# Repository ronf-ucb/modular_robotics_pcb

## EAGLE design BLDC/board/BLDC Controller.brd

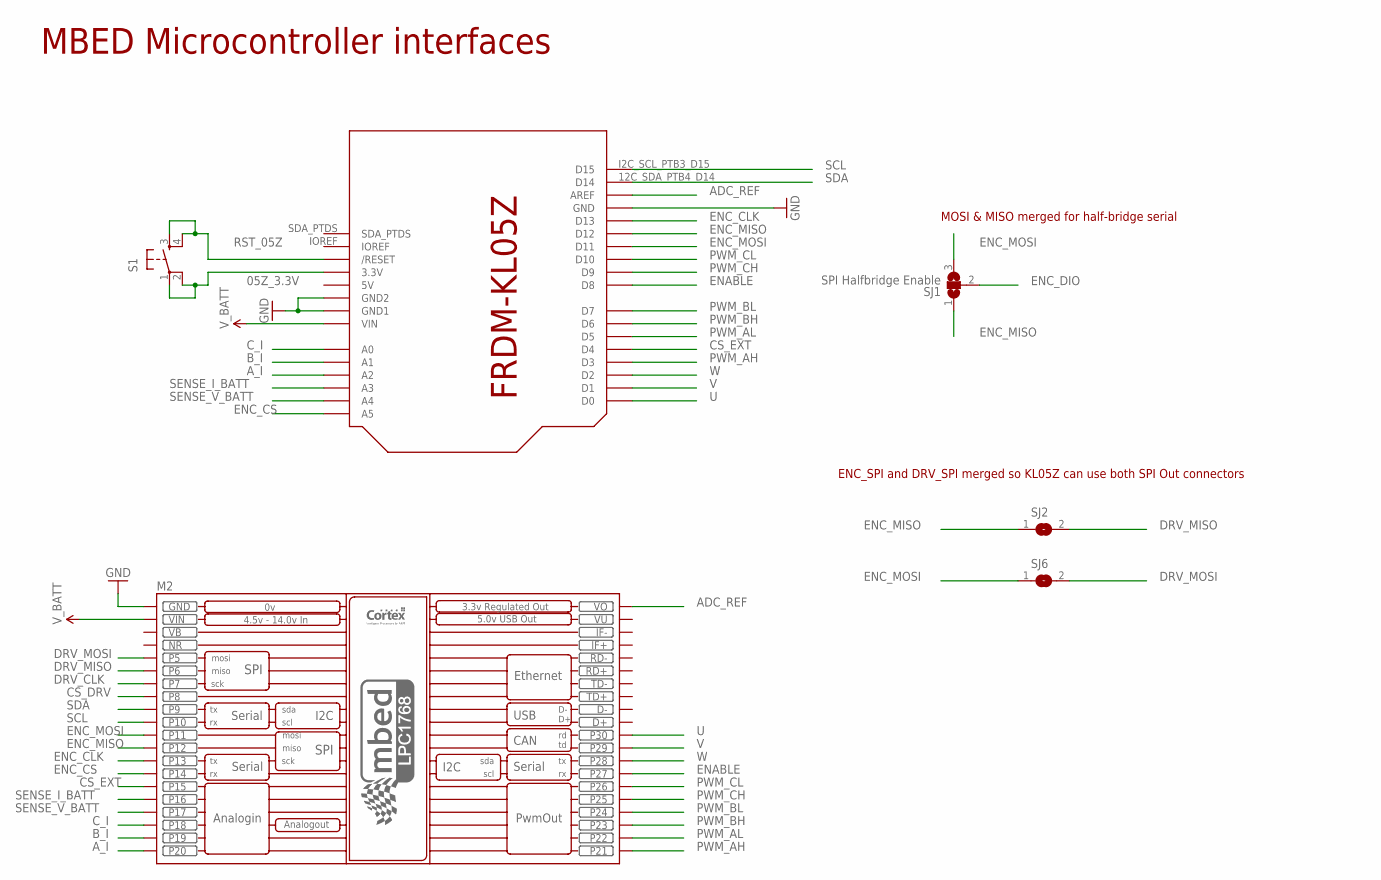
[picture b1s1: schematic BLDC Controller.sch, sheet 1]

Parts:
M1: FRDM-KL05Z; FREESCALEKL05Z
M2: MBED_NXP_LPC1768; MBED-KIT
S1: TAC_SWITCHPTH; TACTILE-PTH
SJ1: SPI Halfbridge Enable; SJ_2
SJ2, SJ6: SJ

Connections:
05Z_3.3V: M1.3.3V, S1.1, S1.2
ADC_REF: M1.AVDD (AREF), M2.VOUT (VO); also elsewhere on the board
A_I: M1.A2_PTA8 (A2), M2.P$20 (P20); also elsewhere on the board
B_I: M1.A1_PTB9 (A1), M2.P$19 (P19); also elsewhere on the board
CS_DRV: M2.P$8 (P8); also elsewhere on the board
CS_EXT: M1.PTA10_D4 (D4), M2.P$15 (P15); also elsewhere on the board
C_I: M1.A0_PTB8 (A0), M2.P$18 (P18); also elsewhere on the board
DRV_CLK: M2.P$7 (P7); also elsewhere on the board
DRV_MISO: M2.P$6 (P6), SJ2.2; also elsewhere on the board
DRV_MOSI: M2.P$5 (P5), SJ6.2; also elsewhere on the board
ENABLE: M1.PTB10_D8 (D8), M2.P$27 (P27); also elsewhere on the board
ENC_CLK: M1.SCK_PTB0_D13 (D13), M2.P$13 (P13); also elsewhere on the board
ENC_CS: M1.A5_PTB13 (A5), M2.P$14 (P14); also elsewhere on the board
ENC_DIO: SJ1.2; also elsewhere on the board
ENC_MISO: M1.MISO_PTA6_D12 (D12), M2.P$12 (P12), SJ1.1, SJ2.1; also elsewhere on the board
ENC_MOSI: M1.MOSI_PTA_D11 (D11), M2.P$11 (P11), SJ1.3, SJ6.1; also elsewhere on the board
GND: M1.GND, M1.GND1, M1.GND2, M2.GND; also elsewhere on the board
NR: M2.NR
PWM_AH: M1.PTB5_D3 (D3), M2.P$21 (P21); also elsewhere on the board
PWM_AL: M1.PTA12_D5 (D5), M2.P$22 (P22); also elsewhere on the board
PWM_BH: M1.PTB6_D6 (D6), M2.P$23 (P23); also elsewhere on the board
PWM_BL: M1.PTB7_D7 (D7), M2.P$24 (P24); also elsewhere on the board
PWM_CH: M1.PTB11_D9 (D9), M2.P$25 (P25); also elsewhere on the board
PWM_CL: M1.PTA_D10 (D10), M2.P$26 (P26); also elsewhere on the board
RST_05Z: M1.RESET (/RESET), S1.3, S1.4
SCL: M1.I2C_SCL_PTB3_D15 (D15), M2.P$10 (P10); also elsewhere on the board
SDA: M1.12C_SDA_PTB4_D14 (D14), M2.P$9 (P9); also elsewhere on the board
SENSE_I_BATT: M1.A3_PTA0 (A3), M2.P$16 (P16); also elsewhere on the board
SENSE_V_BATT: M1.A4_PTA9 (A4), M2.P$17 (P17); also elsewhere on the board
U: M1.TX_PTB2_D0 (D0), M2.P$30 (P30); also elsewhere on the board
V: M1.RX_PTB1_D1 (D1), M2.P$29 (P29); also elsewhere on the board
VB: M2.VB
V_BATT: M1.VIN, M2.VIN; also elsewhere on the board
W: M1.PTA11_D2 (D2), M2.P$28 (P28); also elsewhere on the board

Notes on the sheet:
MBED Microcontroller interfaces
MOSI & MISO merged for half-bridge serial
ENC_SPI and DRV_SPI merged so KL05Z can use both SPI Out connectors

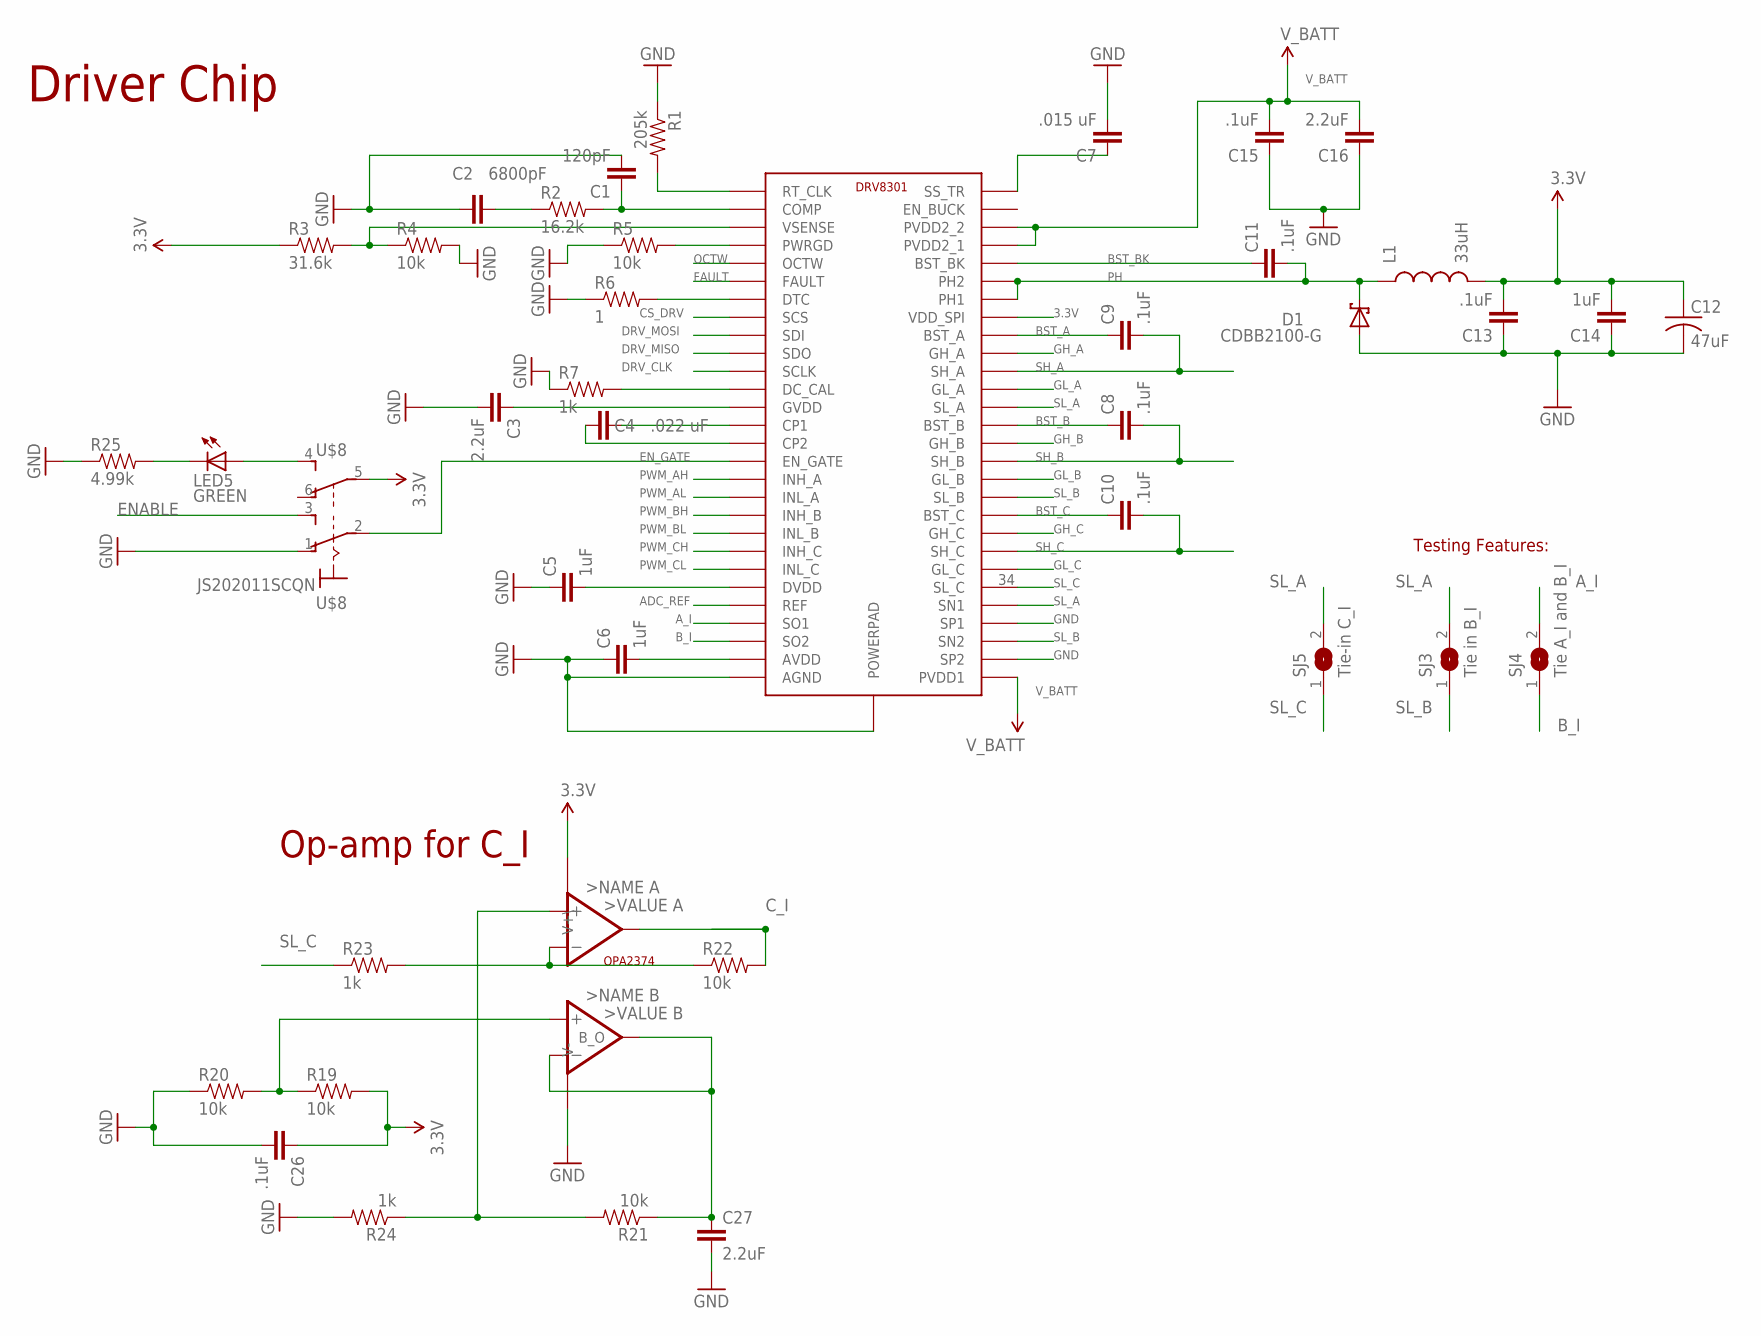
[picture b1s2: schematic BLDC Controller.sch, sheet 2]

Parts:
C1: 120pF; 0402-CAP
C2: 6800pF; 0402-CAP
C3, C16, C27: 2.2uF; 0402-CAP
C4: .022 uF; 0402-CAP
C5, C6, C14: 1uF; 0402-CAP
C7: .015 uF; 0402-CAP
C8, C9, C10, C11, C13, C15, C26: .1uF; 0402-CAP
C12: 47uF; C0603
D1: CDBB2100-G; SMB
IC1: DRV8301
IC2: OPA2374; SOT-23
L1: 33uH; 0805
LED5: GREEN; LED-0603
R1: 205k; 0402-RES
R2: 16.2k; 0402-RES
R3: 31.6k; 0402-RES
R4, R5, R19, R20, R21, R22: 10k; 0402-RES
R6: 1; 0402-RES
R7, R23, R24: 1k; 0402-RES
R25: 4.99k; 0603-RES
SJ3: Tie in B_I; SJ
SJ4: Tie A_I and B_I; SJ
SJ5: Tie-in C_I; SJ
U$8: JS202011SCQN

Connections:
3.3V1: LED5.A, U$8.4 (S); also elsewhere on the board
ADC_REF: IC1.24 (REF); also elsewhere on the board
AVDD: C6.2, IC1.27 (AVDD)
A_I: IC1.25 (SO1), SJ4.2; also elsewhere on the board
BST_A: C9.1, IC1.48 (BST_A)
BST_B: C8.1, IC1.43 (BST_B)
BST_BK: C11.1, IC1.52 (BST_BK)
BST_C: C10.1, IC1.38 (BST_C)
B_I: IC1.26 (SO2), SJ4.1; also elsewhere on the board
CP1: C4.2, IC1.14 (CP1)
CP2: C4.1, IC1.15 (CP2)
CS_DRV: IC1.8 (SCS); also elsewhere on the board
C_I: IC2.1 (A_O), R22.2; also elsewhere on the board
DC_CAL: IC1.12 (DC_CAL), R7.2
DRV_CLK: IC1.11 (SCLK); also elsewhere on the board
DRV_MISO: IC1.10 (SDO); also elsewhere on the board
DRV_MOSI: IC1.9 (SDI); also elsewhere on the board
DTC: IC1.7 (DTC), R6.2
DVDD: C5.2, IC1.23 (DVDD)
EN_GATE: IC1.16 (EN_GATE), U$8.2; also elsewhere on the board
FAULT: IC1.6 (FAULT); also elsewhere on the board
GH_A: IC1.47 (GH_A); also elsewhere on the board
GH_B: IC1.42 (GH_B); also elsewhere on the board
GH_C: IC1.37 (GH_C); also elsewhere on the board
GL_A: IC1.45 (GL_A); also elsewhere on the board
GL_B: IC1.40 (GL_B); also elsewhere on the board
GL_C: IC1.35 (GL_C); also elsewhere on the board
GND: C1.2, C2.2, C3.2, C5.1, C6.1, C7.2, C12.2, C13.1, C14.1, C15.1, C16.1, C26.2, C27.2, D1.A, IC1.28 (AGND), IC1.30 (SP2), IC1.32 (SP1), IC1.EXP@1 (POWERPAD), IC1.EXP@2 (POWERPAD), IC2.4 (V-), R1.1, R4.2, R5.1, R6.1, R7.1, R20.1, R24.2, R25.1, U$8.1 (O); also elsewhere on the board
GVDD: C3.1, IC1.13 (GVDD)
unnamed: C1.1, IC1.2 (COMP), R2.2
unnamed: C2.1, R2.1
unnamed: IC2.8 (B+), R19.1, R20.2
unnamed: C27.1, IC2.6 (B_O), IC2.7 (B-), R21.1
unnamed: IC2.3 (A+), R21.2, R24.1
unnamed: IC2.2 (A-), R22.1, R23.2
unnamed: LED5.C, R25.2
OCTW: IC1.5 (OCTW); also elsewhere on the board
PH: C11.2, D1.C, IC1.50 (PH1), IC1.51 (PH2), L1.1
PWM_AH: IC1.17 (INH_A); also elsewhere on the board
PWM_AL: IC1.18 (INL_A); also elsewhere on the board
PWM_BH: IC1.19 (INH_B); also elsewhere on the board
PWM_BL: IC1.20 (INL_B); also elsewhere on the board
PWM_CH: IC1.21 (INH_C); also elsewhere on the board
PWM_CL: IC1.22 (INL_C); also elsewhere on the board
PWRGD: IC1.4 (PWRGD), R5.2
RT_CLK: IC1.1 (RT_CLK), R1.2
SH_A: C9.2, IC1.46 (SH_A); also elsewhere on the board
SH_B: C8.2, IC1.41 (SH_B); also elsewhere on the board
SH_C: C10.2, IC1.36 (SH_C); also elsewhere on the board
SL_A: IC1.33 (SN1), IC1.44 (SL_A), SJ3.2, SJ5.2; also elsewhere on the board
SL_B: IC1.31 (SN2), IC1.39 (SL_B), SJ3.1; also elsewhere on the board
SL_C: IC1.34 (SL_C), R23.1, SJ5.1; also elsewhere on the board
SS_TR: C7.1, IC1.56 (SS_TR)
VSENSE: IC1.3 (VSENSE), R3.2, R4.1
V_BATT: C15.2, C16.2, IC1.29 (PVDD1), IC1.53 (PVDD2_1), IC1.54 (PVDD2_2); also elsewhere on the board

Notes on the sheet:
Driver Chip
Op-amp for C_I
Testing Features:

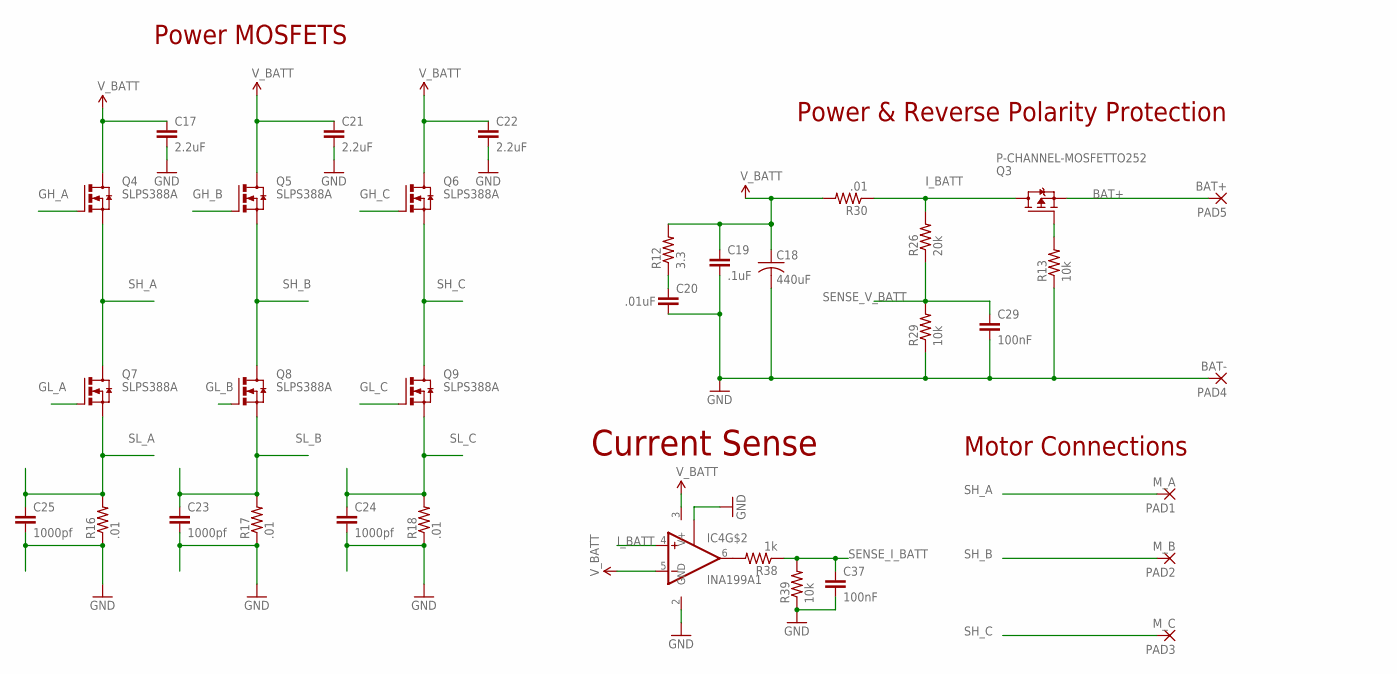
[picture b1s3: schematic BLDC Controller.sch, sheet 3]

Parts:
C17, C21, C22: 2.2uF; 0603-CAP
C18: 440uF; C1210
C19: .1uF; 0402-CAP
C20: .01uF; 0402-CAP
C23, C24, C25: 1000pf; 0603-CAP
C29, C37: 100nF; 0402-CAP
IC4: INA199A1; SC70-6
PAD1: M_A; SMD1,27-2,54
PAD2: M_B; SMD1,27-2,54
PAD3: M_C; SMD1,27-2,54
PAD4: BAT-; SMD1,27-2,54
PAD5: BAT+; SMD1,27-2,54
Q3: P-CHANNEL-MOSFETTO252; TO252
Q4, Q5, Q6, Q7, Q8, Q9: SLPS388A
R12: 3.3; 0402-RES
R13: 10k; 0603-RES
R16, R17, R18, R30: .01; R2010
R26: 20k; 0402-RES
R29, R39: 10k; 0402-RES
R38: 1k; 0402-RES
U$4: INA199A1; SC70-6

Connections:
BAT+: PAD5.1, Q3.2 (S)
GH_A: Q4.4 (G); also elsewhere on the board
GH_B: Q5.4 (G); also elsewhere on the board
GH_C: Q6.4 (G); also elsewhere on the board
GL_A: Q7.4 (G); also elsewhere on the board
GL_B: Q8.4 (G); also elsewhere on the board
GL_C: Q9.4 (G); also elsewhere on the board
GND: C17.2, C18.2, C19.2, C20.2, C21.2, C22.2, C23.2, C24.2, C25.2, C29.2, C37.2, IC4.1 (REF), PAD4.1, R13.1, R16.1, R17.1, R18.1, R29.1, R39.1, U$4.2 (GND); also elsewhere on the board
I_BATT: IC4.4 (+IN), Q3.3 (D), R26.2, R30.1; also elsewhere on the board
unnamed: C20.1, R12.1
unnamed: Q3.1 (G), R13.2
unnamed 56: IC4.6 (OUT), R38.2; also elsewhere on the board
SENSE_I_BATT: C37.1, R38.1, R39.2; also elsewhere on the board
SENSE_V_BATT: C29.1, R26.1, R29.2; also elsewhere on the board
SH_A: PAD1.1, Q4.1 (S), Q4.2 (S), Q4.3 (S), Q7.5 (D), Q7.6 (D), Q7.7 (D), Q7.8 (D), Q7.PAD (D); also elsewhere on the board
SH_B: PAD2.1, Q5.1 (S), Q5.2 (S), Q5.3 (S), Q8.5 (D), Q8.6 (D), Q8.7 (D), Q8.8 (D), Q8.PAD (D); also elsewhere on the board
SH_C: PAD3.1, Q6.1 (S), Q6.2 (S), Q6.3 (S), Q9.5 (D), Q9.6 (D), Q9.7 (D), Q9.8 (D), Q9.PAD (D); also elsewhere on the board
SL_A: C25.1, Q7.1 (S), Q7.2 (S), Q7.3 (S), R16.2; also elsewhere on the board
SL_B: C23.1, Q8.1 (S), Q8.2 (S), Q8.3 (S), R17.2; also elsewhere on the board
SL_C: C24.1, Q9.1 (S), Q9.2 (S), Q9.3 (S), R18.2; also elsewhere on the board
V_BATT: C17.1, C18.1, C19.1, C21.1, C22.1, IC4.5 (-IN), Q4.5 (D), Q4.6 (D), Q4.7 (D), Q4.8 (D), Q4.PAD (D), Q5.5 (D), Q5.6 (D), Q5.7 (D), Q5.8 (D), Q5.PAD (D), Q6.5 (D), Q6.6 (D), Q6.7 (D), Q6.8 (D), Q6.PAD (D), R12.2, R30.2, U$4.3 (V+); also elsewhere on the board

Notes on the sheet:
Power MOSFETS
Power & Reverse Polarity Protection
Motor Connections
Current Sense

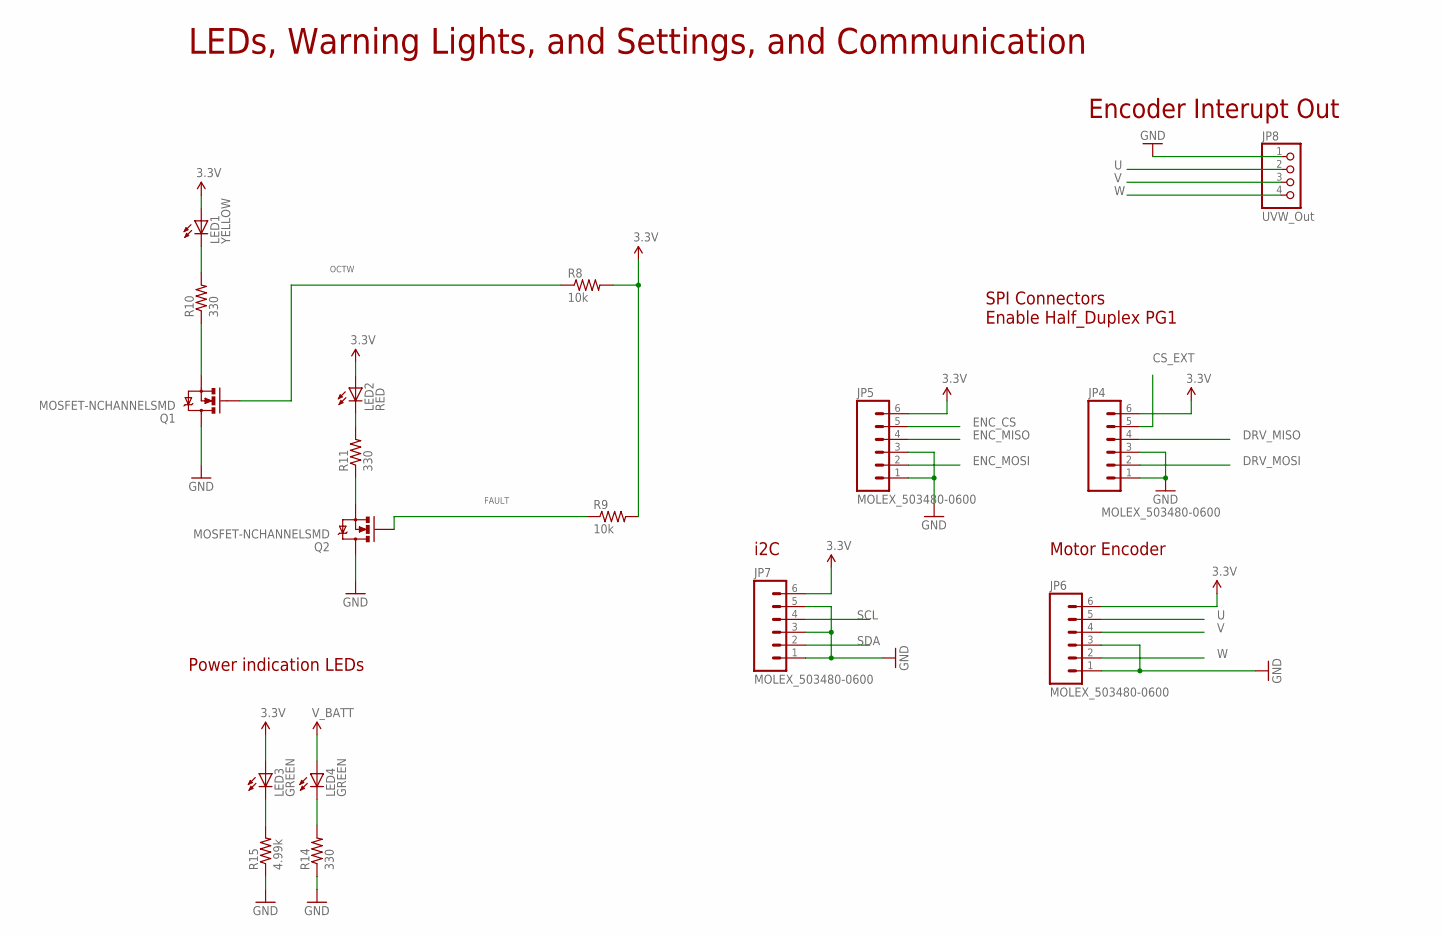
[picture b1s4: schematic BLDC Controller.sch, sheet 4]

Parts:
JP4, JP5, JP6, JP7: MOLEX_503480-0600
JP8: UVW_Out; 1X04
LED1: YELLOW; LED-0603
LED2: RED; LED-0603
LED3, LED4: GREEN; LED-0603
Q1, Q2: MOSFET-NCHANNELSMD; SOT23-3
R8, R9: 10k; 0402-RES
R10, R11, R14: 330; 0603-RES
R15: 4.99k; 0603-RES

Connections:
CS_EXT: JP4.5; also elsewhere on the board
DRV_MISO: JP4.4; also elsewhere on the board
DRV_MOSI: JP4.2; also elsewhere on the board
ENC_CS: JP5.5; also elsewhere on the board
ENC_MISO: JP5.4; also elsewhere on the board
ENC_MOSI: JP5.2; also elsewhere on the board
FAULT: Q2.1 (G), R9.1; also elsewhere on the board
GND: JP4.1, JP4.3, JP5.1, JP5.3, JP6.1, JP6.3, JP7.1, JP7.3, JP7.5, JP8.1, Q1.3 (D), Q2.3 (D), R14.1, R15.1; also elsewhere on the board
unnamed: LED1.C, R10.2
unnamed: LED2.C, R11.2
unnamed: Q1.2 (S), R10.1
unnamed: Q2.2 (S), R11.1
unnamed: LED3.C, R15.2
unnamed: LED4.C, R14.2
OCTW: Q1.1 (G), R8.1; also elsewhere on the board
SCL: JP7.4; also elsewhere on the board
SDA: JP7.2; also elsewhere on the board
U: JP6.5, JP8.2; also elsewhere on the board
V: JP6.4, JP8.3; also elsewhere on the board
V_BATT: LED4.A; also elsewhere on the board
W: JP6.2, JP8.4; also elsewhere on the board

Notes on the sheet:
LEDs, Warning Lights, and Settings, and Communication
Power indication LEDs
Encoder Interupt Out
i2C
Motor Encoder
SPI Connectors Enable Half_Duplex PG1

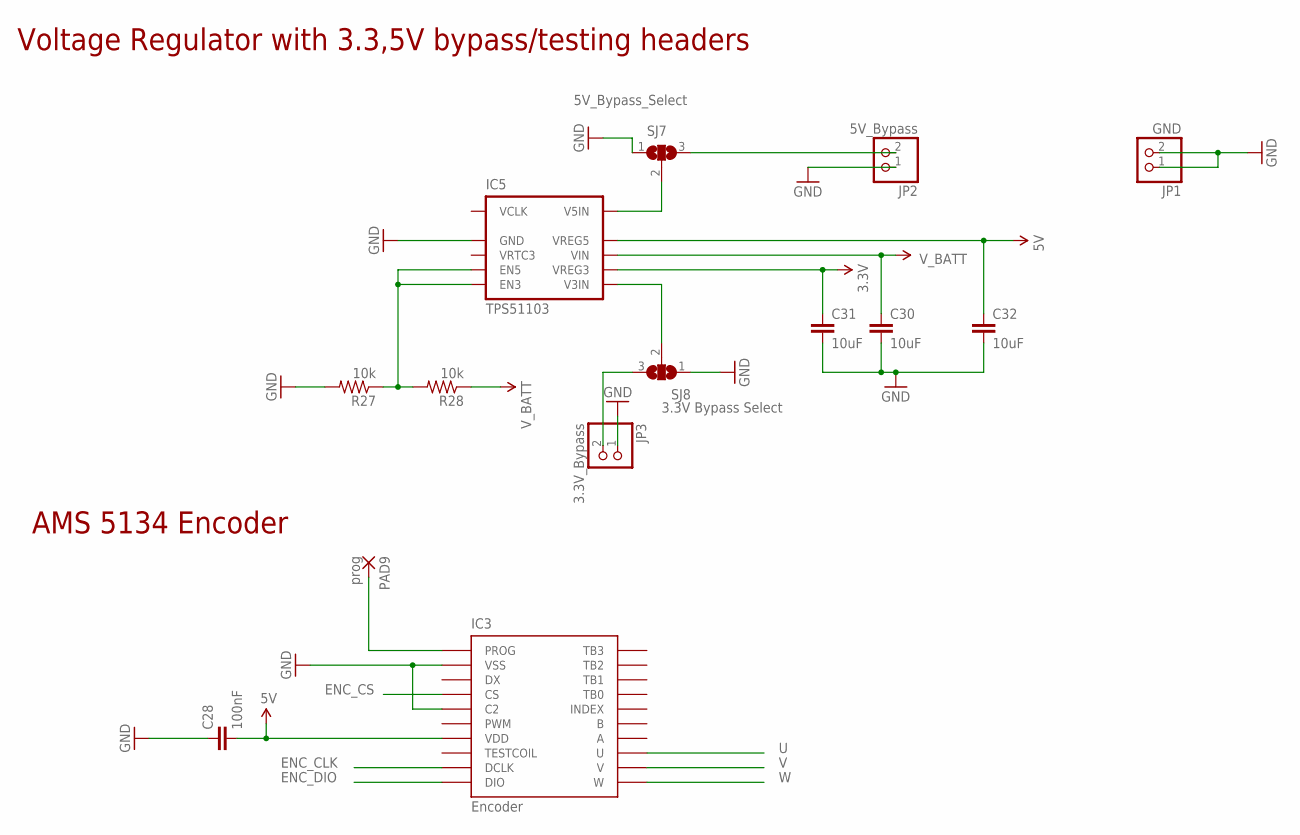
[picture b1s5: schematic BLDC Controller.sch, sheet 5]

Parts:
C28: 100nF; 0402-CAP
C30, C31, C32: 10uF; 0603-CAP
IC3: Encoder; AS5134
IC5: TPS51103; DRC(S-PVSON-N10)
JP1: GND; 1X02
JP2: 5V_Bypass; 1X02
JP3: 3.3V_Bypass; 1X02
PAD9: prog; SMD1,27-2,54
R27, R28: 10k; 0402-RES
SJ7: 5V_Bypass_Select; SJ_2
SJ8: 3.3V Bypass Select; SJ_2

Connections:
ENC_CLK: IC3.9 (DCLK); also elsewhere on the board
ENC_CS: IC3.4 (CS); also elsewhere on the board
ENC_DIO: IC3.10 (DIO); also elsewhere on the board
GND: C28.1, C30.2, C31.2, C32.2, IC3.2 (VSS), IC3.5 (C2), IC5.2 (GND), IC5.TH (GND), JP1.1, JP1.2, JP2.1, JP3.1, R27.2, SJ7.1, SJ8.1; also elsewhere on the board
unnamed: JP2.2, SJ7.3
unnamed: JP3.2, SJ8.3
unnamed: IC3.1 (PROG), PAD9.1
PWR_ENABLE1: IC5.4 (EN5), IC5.5 (EN3), R27.1, R28.2
U: IC3.11 (U); also elsewhere on the board
V: IC3.12 (V); also elsewhere on the board
V3IN1: IC5.6 (V3IN), SJ8.2
V5IN1: IC5.10 (V5IN), SJ7.2
V_BATT: C30.1, IC5.8 (VIN), R28.1; also elsewhere on the board
W: IC3.13 (W); also elsewhere on the board

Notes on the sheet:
Voltage Regulator with 3.3,5V bypass/testing headers
AMS 5134 Encoder

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
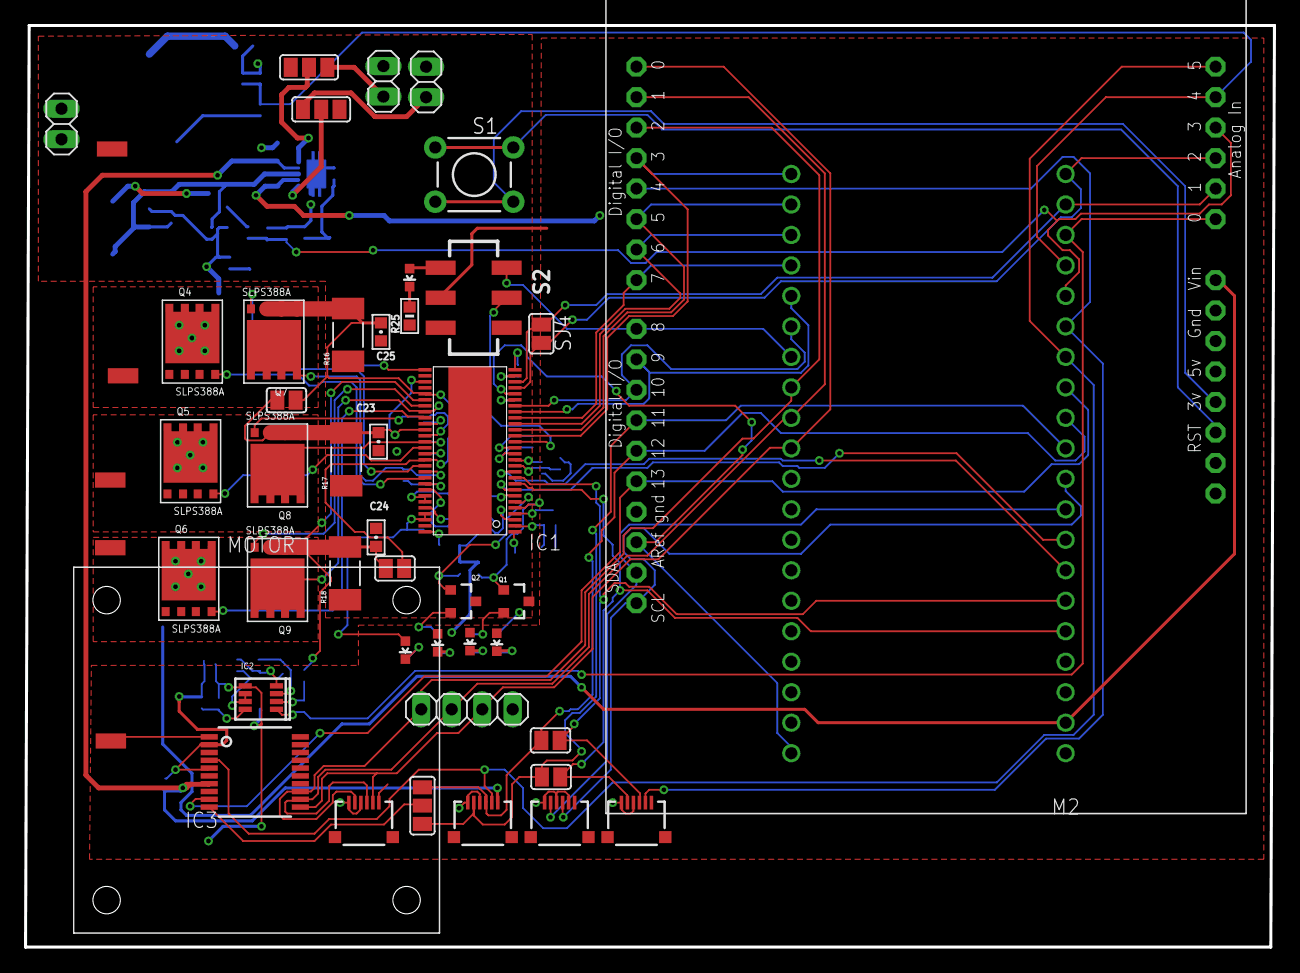
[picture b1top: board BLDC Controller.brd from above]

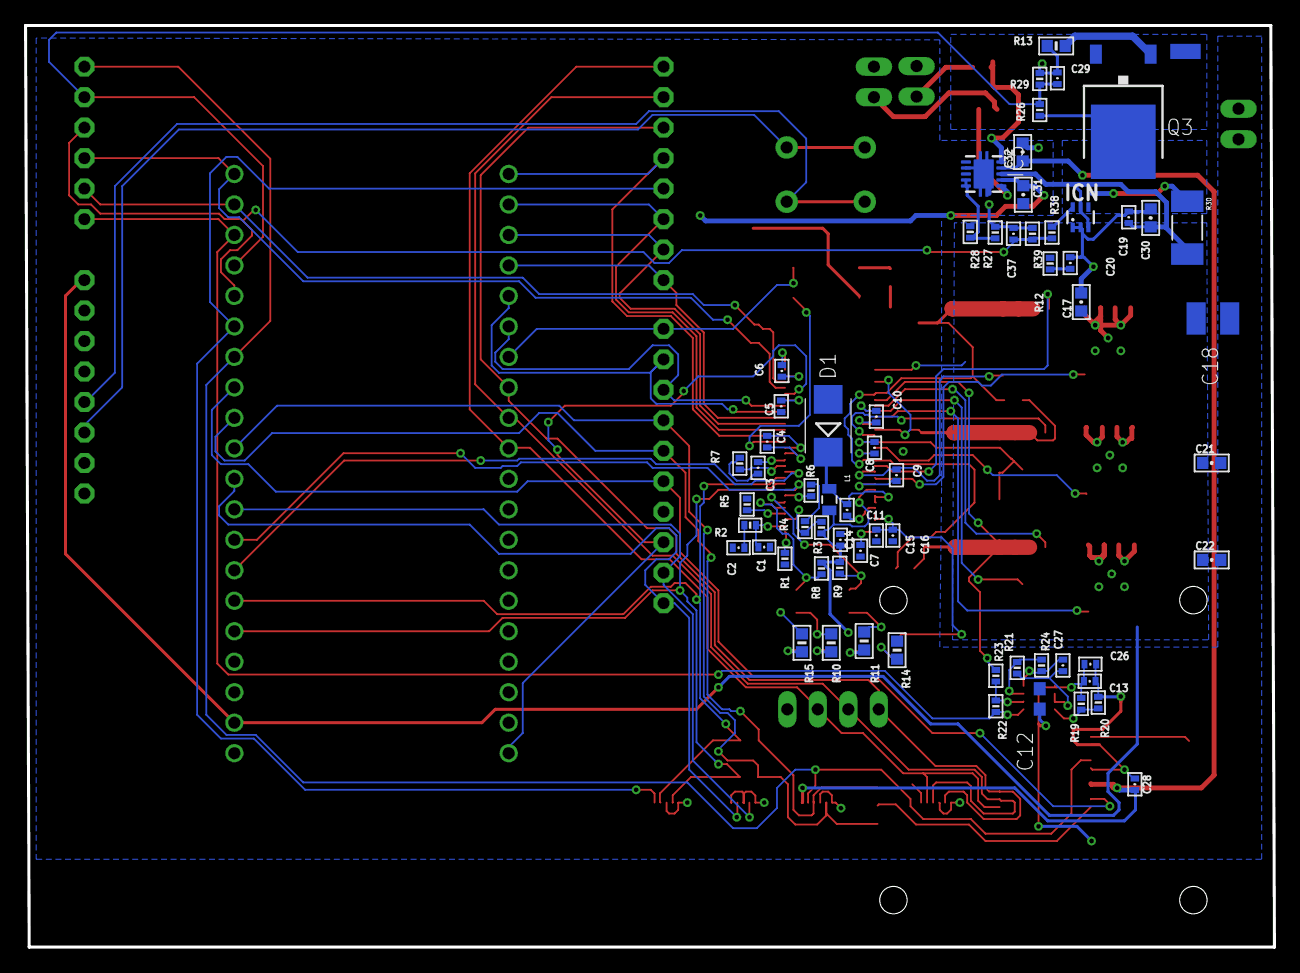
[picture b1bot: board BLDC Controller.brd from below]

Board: 2 copper layers, 104.1 x 76.8 mm, 113 parts (64 on the bottom side), 90 nets.

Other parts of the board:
ICN: INA199A1; SC70-6
MOTOR: S-1804MOTOR
S2: JS202011SCQN

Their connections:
3.3V1: S2.4; also elsewhere on the board
ENABLE: S2.3; also elsewhere on the board
EN_GATE: S2.2; also elsewhere on the board
GND: ICN.1, ICN.2, S2.1; also elsewhere on the board
I_BATT: ICN.4; also elsewhere on the board
unnamed 56: ICN.6; also elsewhere on the board
V_BATT: ICN.3, ICN.5; also elsewhere on the board

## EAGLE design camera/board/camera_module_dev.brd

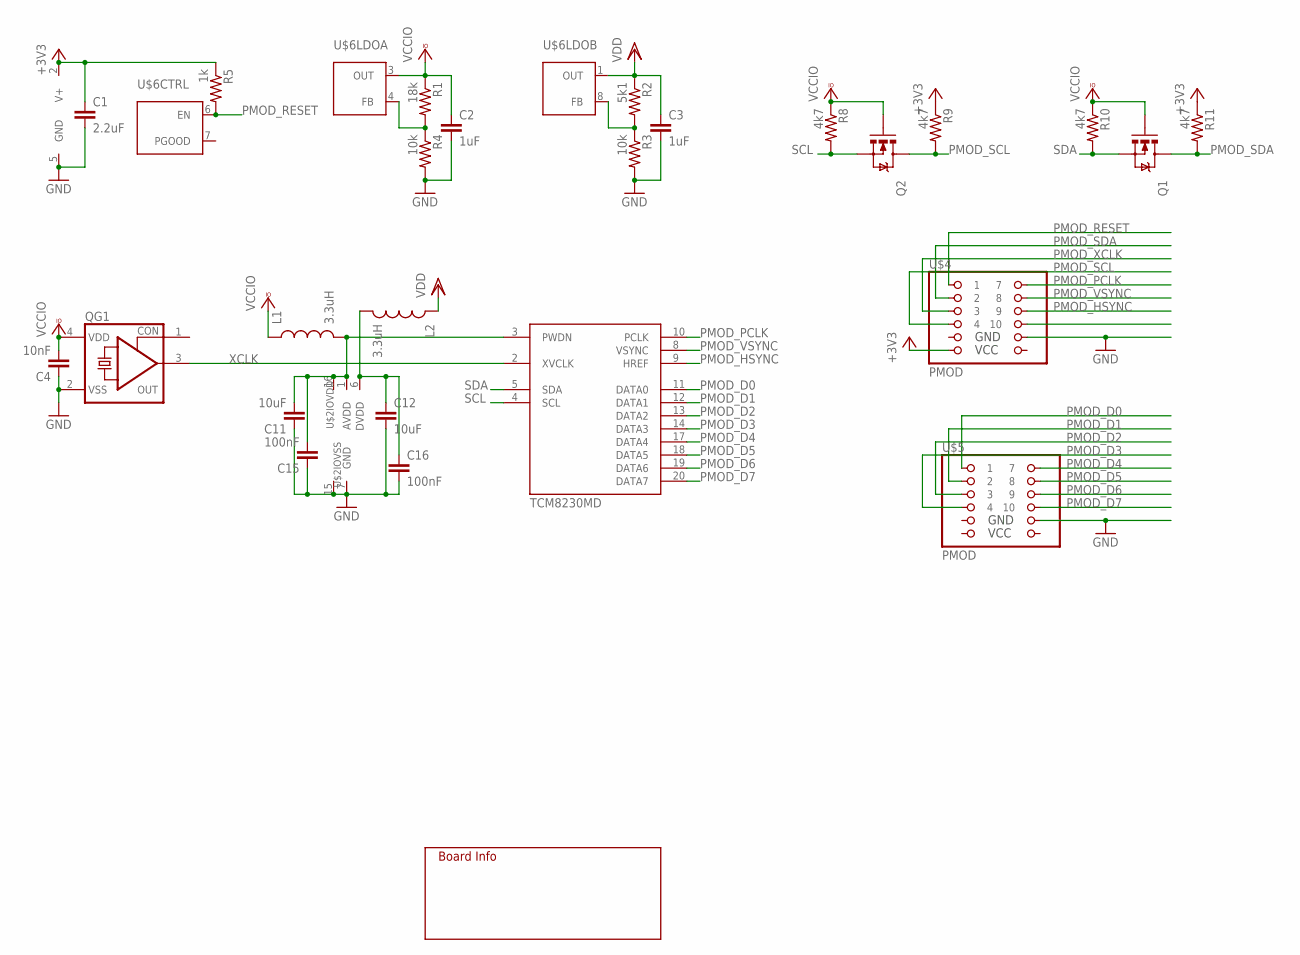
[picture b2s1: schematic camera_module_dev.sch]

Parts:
C1: 2.2uF; 0402-CAP; VOLTAGE 6.3V
C2, C3: 1uF; 0402-CAP; VOLTAGE 6.3V
C4: 10nF; 0402-CAP; VOLTAGE 6.3V
C11, C12: 10uF; 0603-CAP; VOLTAGE 6.3V
C15, C16: 100nF; 0402-CAP; VOLTAGE 6.3V
L1, L2: 3.3uH; 1007
Q1, Q2: MOSFET-NCHANNELBSS123LT1G; SOT23
QG1: CRYSTAL_RES--SMD-4; SMD-4
R1: 18k; 0402-RES
R2: 5k1; 0402-RES
R3, R4: 10k; 0402-RES
R5: 1k; 0402-RES
R8, R9, R10, R11: 4k7; 0402-RES
U$2: TCM8230MD; TCM-20
U$4, U$5: PMOD; 2X06
U$6: SC560C; MLPQ-UT8
U$7: INFO

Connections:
+3V3: C1.1, R5.1, R9.1, R11.1, U$4.11 (6), U$6.2 (V+)
GND: C1.2, C2.2, C3.2, C4.1, C11.1, C12.2, C15.1, C16.2, QG1.2 (VSS), R3.2, R4.2, U$2.7 (GND), U$2.15 (V), U$4.10 (11), U$5.10 (11), U$6.5 (GND)
unnamed: C12.1, C16.1, L2.2, U$2.6 (DVDD)
unnamed: C11.2, C15.2, L1.2, U$2.1 (AVDD), U$2.3 (PWDN), U$2.16 (V)
unnamed: R1.2, R4.1, U$6.4 (FB)
unnamed: R2.2, R3.1, U$6.8 (FB)
PMOD_D0: U$2.11 (DATA0), U$5.1
PMOD_D1: U$2.12 (DATA1), U$5.3 (2)
PMOD_D2: U$2.13 (DATA2), U$5.5 (3)
PMOD_D3: U$2.14 (DATA3), U$5.7 (4)
PMOD_D4: U$2.17 (DATA4), U$5.2 (7)
PMOD_D5: U$2.18 (DATA5), U$5.4 (8)
PMOD_D6: U$2.19 (DATA6), U$5.6 (9)
PMOD_D7: U$2.20 (DATA7), U$5.8 (10)
PMOD_HSYNC: U$2.9 (HREF), U$4.6 (9)
PMOD_PCLK: U$2.10 (PCLK), U$4.2 (7)
PMOD_RESET: R5.2, U$4.1, U$6.6 (EN)
PMOD_SCL: Q2.3 (D), R9.2, U$4.7 (4)
PMOD_SDA: Q1.3 (D), R11.2, U$4.3 (2)
PMOD_VSYNC: U$2.8 (VSYNC), U$4.4 (8)
PMOD_XCLK: U$4.5 (3)
SCL: Q2.2 (S), R8.2, U$2.4 (SCL)
SDA: Q1.2 (S), R10.2, U$2.5 (SDA)
VCCIO: C2.1, C4.2, L1.1, Q1.1 (G), Q2.1 (G), QG1.4 (VDD), R1.1, R8.1, R10.1, U$6.3 (OUT)
VDD: C3.1, L2.1, R2.1, U$6.1 (OUT)
XCLK: QG1.3 (OUT), U$2.2 (XVCLK)

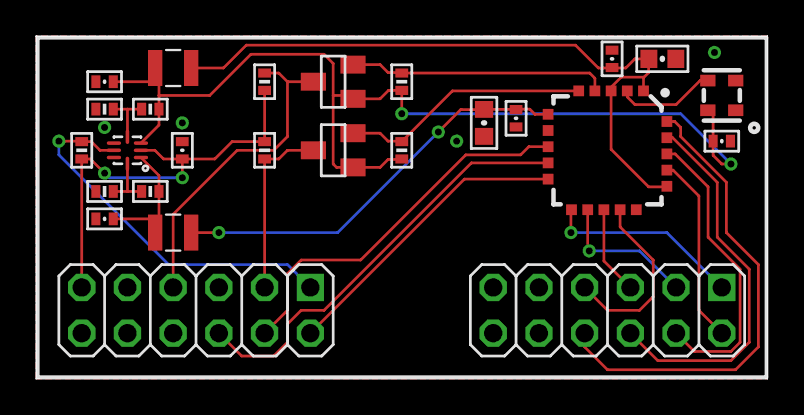
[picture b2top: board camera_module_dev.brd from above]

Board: 4 copper layers, 40.6 x 19.1 mm, 27 parts (1 on the bottom side), 25 nets.

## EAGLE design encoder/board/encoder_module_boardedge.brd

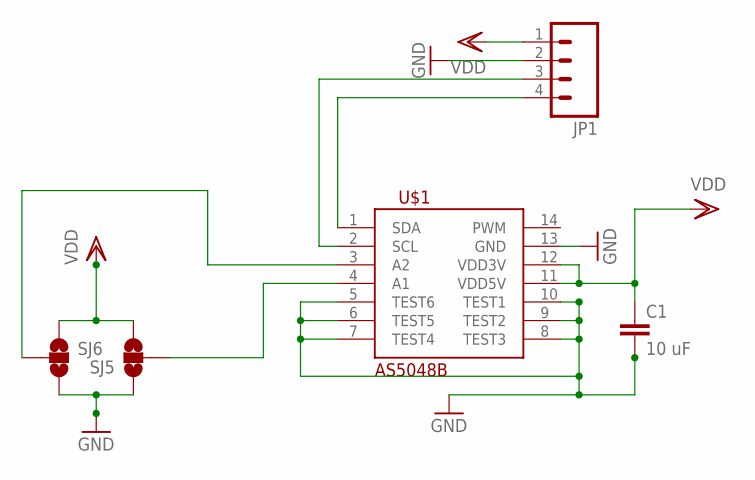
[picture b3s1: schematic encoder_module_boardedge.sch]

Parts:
C1: 10 uF; 0603-CAP
JP1: M04BOARDEDGE_VERT_VIA; 1X4_3MM_BOARDEDGE_VERT_VIA
SJ5, SJ6: SOLDERJUMPER_2WAYS; SJ_3
U$1: AS5048B; TSSOP14

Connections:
A1: SJ5.2, U$1.4 (A1)
A2: SJ6.2, U$1.3 (A2)
GND: C1.2, JP1.2, SJ5.1, SJ6.3, U$1.5 (TEST6), U$1.6 (TEST5), U$1.7 (TEST4), U$1.8 (TEST3), U$1.9 (TEST2), U$1.10 (TEST1), U$1.13 (GND)
unnamed: JP1.4, U$1.1 (SDA)
unnamed: JP1.3, U$1.2 (SCL)
VDD: C1.1, JP1.1, SJ5.3, SJ6.1, U$1.11 (VDD5V), U$1.12 (VDD3V)

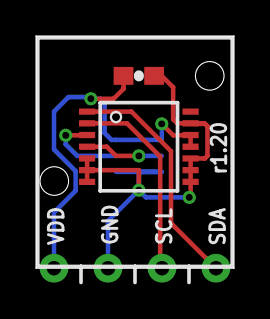
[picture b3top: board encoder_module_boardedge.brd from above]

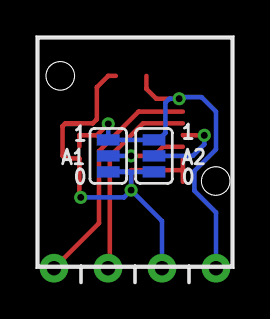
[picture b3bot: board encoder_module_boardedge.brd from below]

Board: 4 copper layers, 11.0 x 12.9 mm, 5 parts (2 on the bottom side), 6 nets.

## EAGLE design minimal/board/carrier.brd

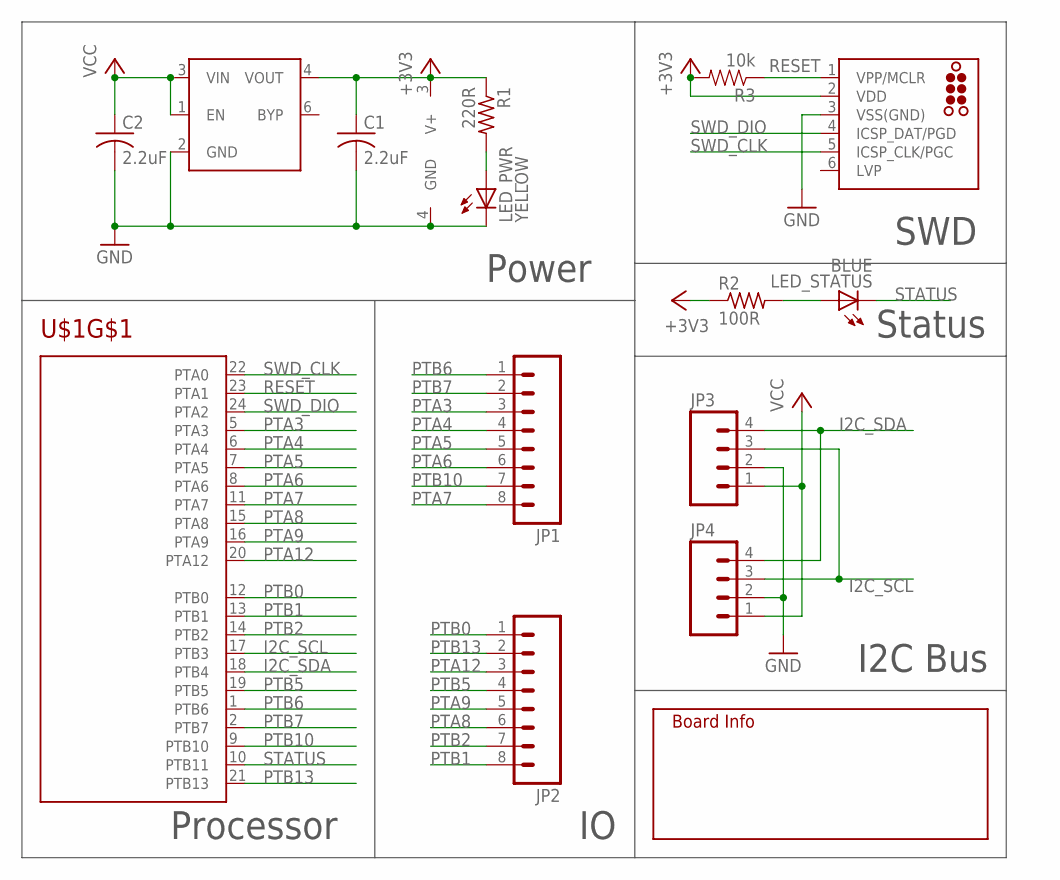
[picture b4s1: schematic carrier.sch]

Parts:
C1, C2: 2.2uF; C0402
J1: TC2030-MCP-NL
JP1, JP2: M081X08; 1X08
JP3, JP4: M04PTH; 1X04
LED_PWR: YELLOW; SML0603
LED_STATUS: BLUE; SML0603
R1: 220R; R0402
R2: 100R; R0402
R3: 10k; 0402-RES
U$1: MKL05Z32VFK4-QFN; QFN-24
U$2: MIC5305-MLF; MLF-6
U$3: INFO

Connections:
+3V3: C1.1, J1.2 (VDD), R1.1, R2.1, R3.2, U$1.3 (V+), U$2.4 (VOUT)
GND: C1.2, C2.2, J1.3 (VSS(GND)), JP3.2, JP4.2, LED_PWR.C, U$1.4 (GND), U$2.2 (GND)
I2C_SCL: JP3.3, JP4.3, U$1.17 (PTB3)
I2C_SDA: JP3.4, JP4.4, U$1.18 (PTB4)
unnamed: LED_PWR.A, R1.2
unnamed: LED_STATUS.A, R2.2
PTA3: JP1.3, U$1.5 (PTA3)
PTA4: JP1.4, U$1.6 (PTA4)
PTA5: JP1.5, U$1.7 (PTA5)
PTA6: JP1.6, U$1.8 (PTA6)
PTA7: JP1.8, U$1.11 (PTA7)
PTA8: JP2.6, U$1.15 (PTA8)
PTA9: JP2.5, U$1.16 (PTA9)
PTA12: JP2.3, U$1.20 (PTA12)
PTB0: JP2.1, U$1.12 (PTB0)
PTB1: JP2.8, U$1.13 (PTB1)
PTB2: JP2.7, U$1.14 (PTB2)
PTB5: JP2.4, U$1.19 (PTB5)
PTB6: JP1.1, U$1.1 (PTB6)
PTB7: JP1.2, U$1.2 (PTB7)
PTB10: JP1.7, U$1.9 (PTB10)
PTB13: JP2.2, U$1.21 (PTB13)
RESET: J1.1 (VPP/MCLR), R3.1, U$1.23 (PTA1)
STATUS: LED_STATUS.C, U$1.10 (PTB11)
SWD_CLK: J1.5 (ICSP_CLK/PGC), U$1.22 (PTA0)
SWD_DIO: J1.4 (ICSP_DAT/PGD), U$1.24 (PTA2)
VCC: C2.1, JP3.1, JP4.1, U$2.1 (EN), U$2.3 (VIN)

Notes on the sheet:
Processor
Power
SWD
Status
I2C Bus

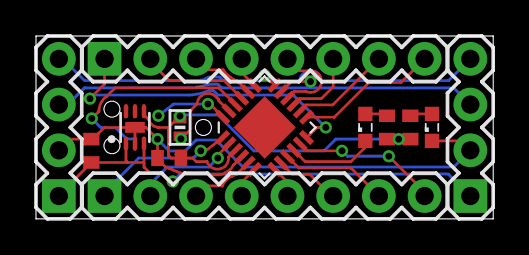
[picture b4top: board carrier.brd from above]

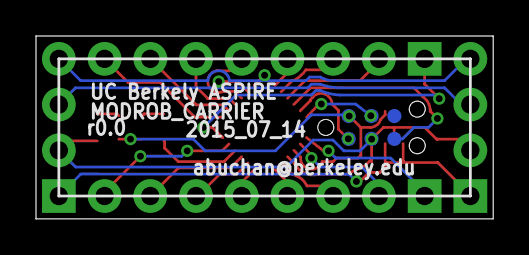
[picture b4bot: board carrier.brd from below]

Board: 2 copper layers, 25.4 x 10.2 mm, 15 parts (2 on the bottom side), 27 nets.

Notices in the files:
parts and their libraries:
biomimetic: UC Regents. All rights reserved.
SparkFun-DiscreteSemi: Licensing: CC v3.0 Share-Alike You are welcome to use this library for commercial purposes.
tag-connect: ©2009 ROFA.cz - modified and updated by Robert Darlington ‹rdarlington@gmail.com›
